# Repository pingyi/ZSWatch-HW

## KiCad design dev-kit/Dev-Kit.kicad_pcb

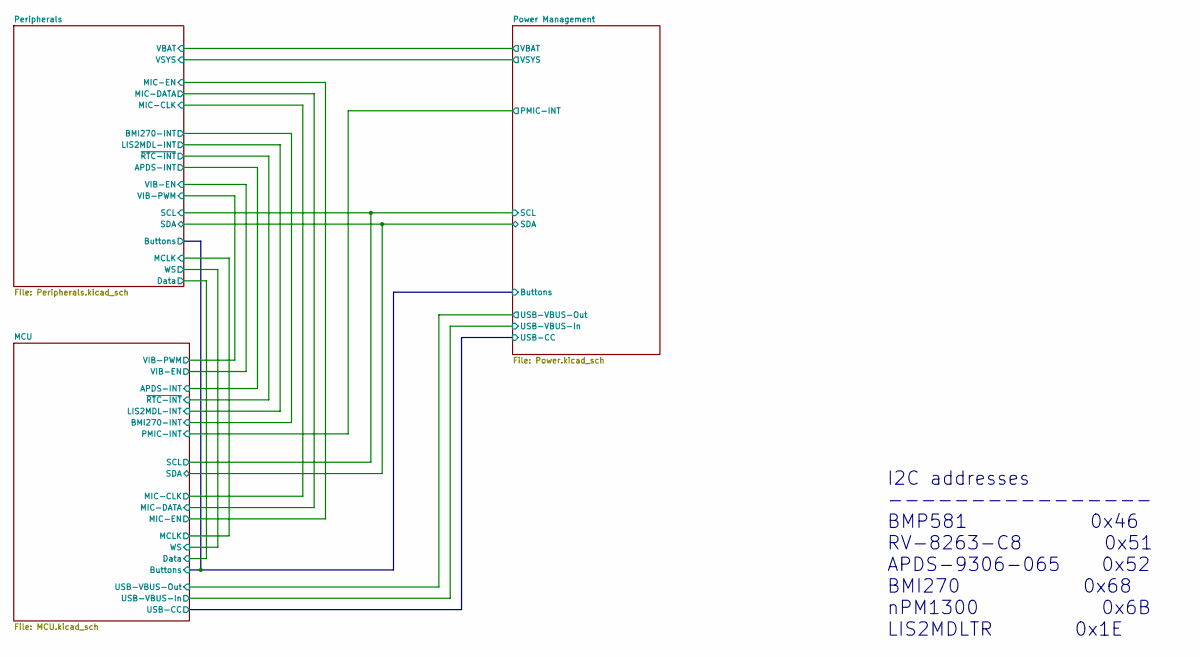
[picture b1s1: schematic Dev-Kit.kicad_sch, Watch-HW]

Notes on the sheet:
I2C addresses ---------------- BMP581 0x46 RV-8263-C8 0x51 APDS-9306-065 0x52 BMI270 0x68 nPM1300 0x6B LIS2MDLTR 0x1E

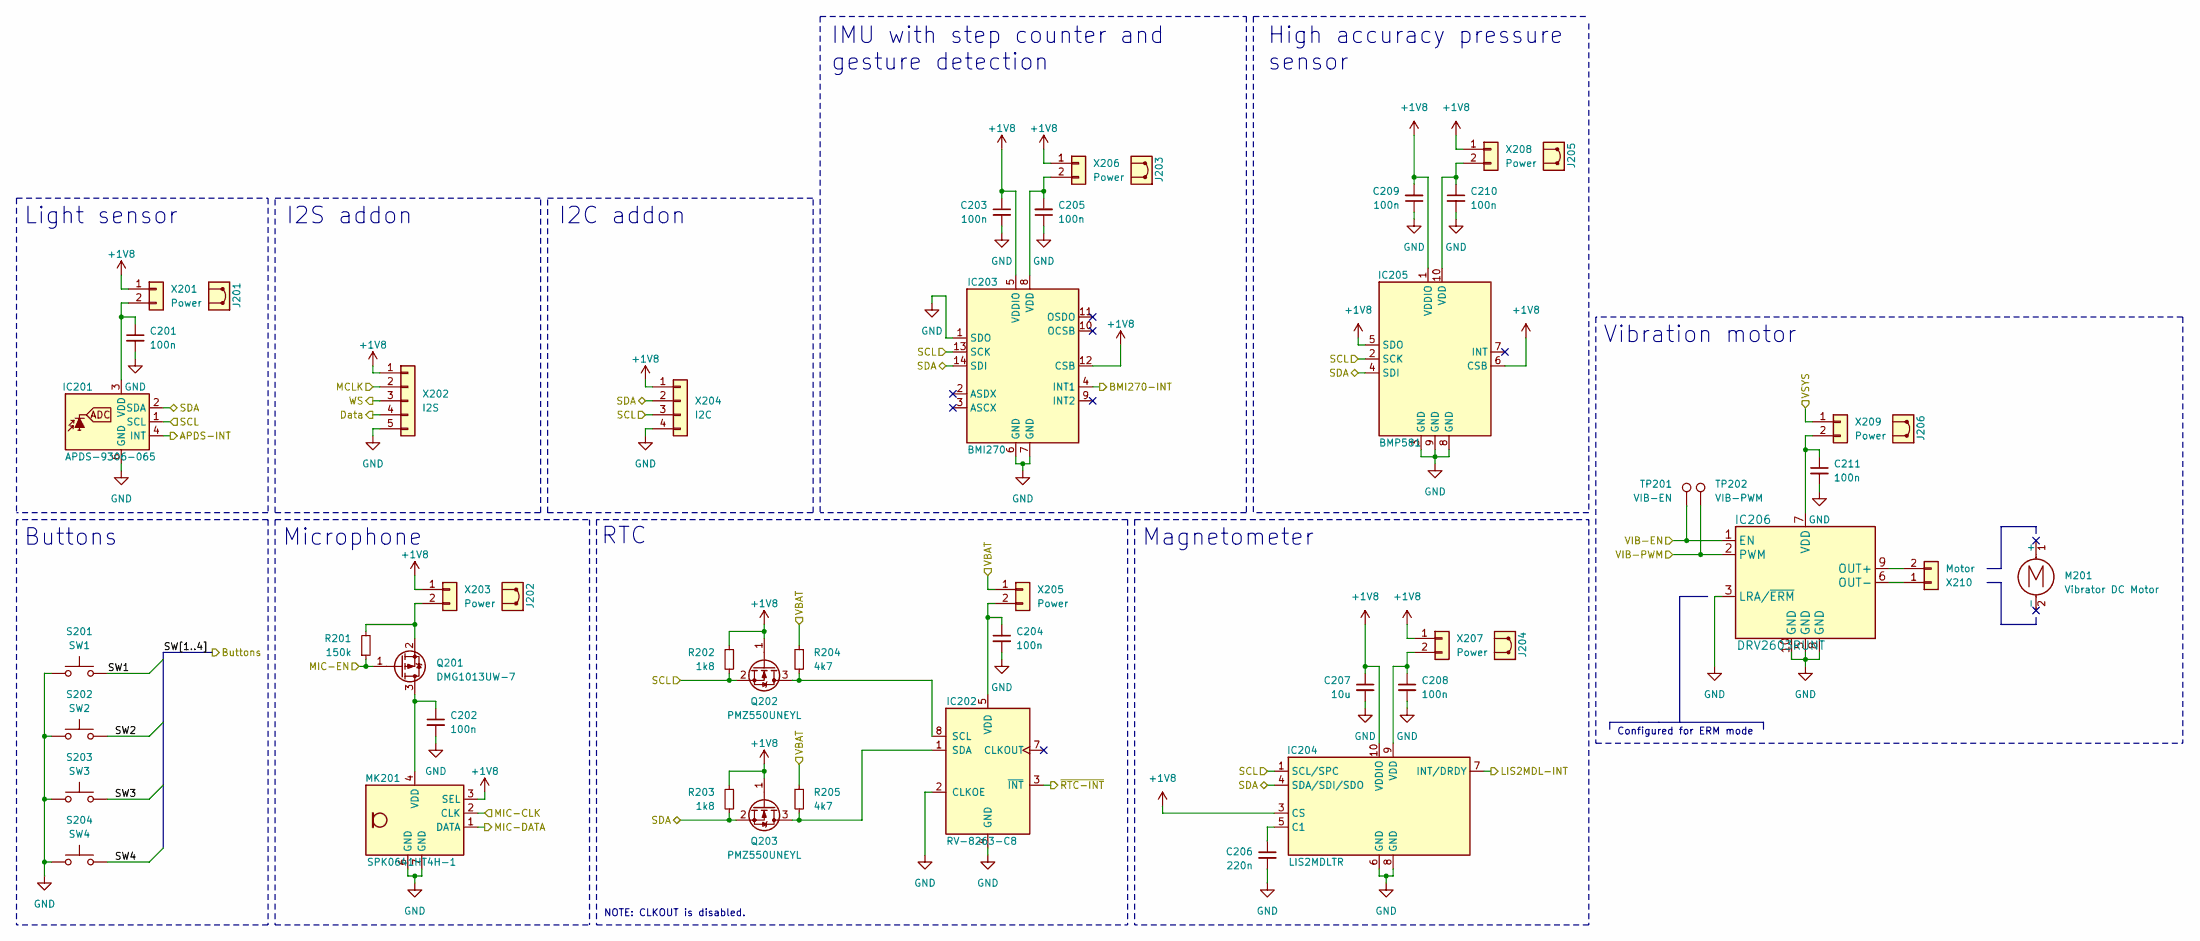
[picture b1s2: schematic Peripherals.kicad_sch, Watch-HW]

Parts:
C201, C202, C203, C204, C205, C208, C209, C210, C211: 100n; C_0402_1005Metric; mouser# 581-0402ZC104KAT4A
C206: 220n; C_0402_1005Metric; mouser# 581-04023C224KAT2A
C207: 10u; C_0402_1005Metric; mouser# 81-GRJ155R60J106ME11D
IC201: APDS-9306-065; Broadcom_DFN-6_2x2mm_P0.65mm; mouser# 630-APDS-9306-065
IC202: RV-8263-C8; mouser# 428-204291-MC01
IC203: BMI270; Bosch_LGA-14_3x2.5mm_P0.5mm_LayoutBorder3x4y; mouser# 262-BMI270
IC204: LIS2MDLTR; LGA-12_2x2mm_P0.5mm; mouser# 511-LIS2MDLTR
IC205: BMP581; Bosch_LGA-10_2x2mm_P0.5mm_ClockwisePinNumbering; mouser# 262-BMP581
IC206: DRV2603RUNT; WQFN-10_2x2mm_P0.5mm; mouser# 595-DRV2603RUNT
J201, J202, J203, J204, J205, J206: Jumper; mouser# 710-60900213421
M201: Vibrator DC Motor; digikey# 1670-VC1027B902F-ND
MK201: SPK0641HT4H-1; mouser# 721-SPK0641HT4H-1
Q201: DMG1013UW-7; SOT-323_SC-70; mouser# 621-DMG1013UW-7
Q202, Q203: PMZ550UNEYL; SOT-883; mouser# 771-PMZ550UNEYL
R201: 150k; R_0402_1005Metric; mouser# 603-RC0404FR-07150KL
R202, R203: 1k8; R_0402_1005Metric; mouser# 603-RC0402FR-074K7L
R204, R205: 4k7; R_0402_1005Metric; mouser# 603-RC0402FR-074K7L
S201: SW1; WS-TASV-6x6; mouser# 710-430182050816
S202: SW2; WS-TASV-6x6; mouser# 710-430182050816
S203: SW3; WS-TASV-6x6; mouser# 710-430182050816
S204: SW4; WS-TASV-6x6; mouser# 710-430182050816
TP201: VIB-EN; TestPoint_Pad_D1.0mm
TP202: VIB-PWM; TestPoint_Pad_D1.0mm
X201, X203, X205, X206, X207, X208, X209: Power; PinHeader_1x02_P2.54mm_Vertical_SMD_Pin1Left; mouser# 649-1012938090201BLF
X202: I2S; PinHeader_1x05_P2.54mm_Vertical_SMD_Pin1Left; mouser# 649-10129380-905002ALF
X204: I2C; PinHeader_1x04_P2.54mm_Vertical_SMD_Pin1Left; mouser# 649-10129380-904002ALF
X210: Motor; 78171-0002; mouser# 538-78171-0002

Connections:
+1V8: C203.1, C207.1, C209.2, IC203.5 (VDDIO), IC203.12 (CSB), IC204.3 (CS), IC204.10 (VDDIO), IC205.1 (VDDIO), IC205.5 (SDO), IC205.6 (CSB), MK201.3 (SEL), Q202.1 (G), Q203.1 (G), R202.1, R203.1, X201.1, X202.1, X203.1, X204.1, X206.1, X207.1, X208.1; also elsewhere on the board
/MCU/APDS-INT: IC201.4 (INT); also elsewhere on the board
/MCU/BMI270-INT: IC203.4 (INT1); also elsewhere on the board
/MCU/Data: X202.4; also elsewhere on the board
/MCU/LIS2MDL-INT: IC204.7 (INT/DRDY); also elsewhere on the board
/MCU/MCLK: X202.2; also elsewhere on the board
/MCU/MIC-CLK: MK201.2 (CLK); also elsewhere on the board
/MCU/MIC-DATA: MK201.1 (DATA); also elsewhere on the board
/MCU/MIC-EN: Q201.1 (G), R201.1; also elsewhere on the board
/MCU/SCL: IC201.1 (SCL), IC203.13 (SCK), IC204.1 (SCL/SPC), IC205.2 (SCK), Q202.2 (S), R202.2, X204.3; also elsewhere on the board
/MCU/SDA: IC201.2 (SDA), IC203.14 (SDI), IC204.4 (SDA/SDI/SDO), IC205.4 (SDI), Q203.2 (S), R203.2, X204.2; also elsewhere on the board
/MCU/SW1: S201.1; also elsewhere on the board
/MCU/SW2: S202.2; also elsewhere on the board
/MCU/SW3: S203.2; also elsewhere on the board
/MCU/SW4: S204.1; also elsewhere on the board
/MCU/VIB-EN: IC206.1 (EN), TP201.1; also elsewhere on the board
/MCU/VIB-PWM: IC206.2 (PWM), TP202.1; also elsewhere on the board
/MCU/WS: X202.3; also elsewhere on the board
/MCU/~RTC-INT: IC202.3 (~INT); also elsewhere on the board
/Peripherals/VBAT: R204.1, R205.1, X205.1; also elsewhere on the board
/Peripherals/VSYS: X209.1; also elsewhere on the board
GND: C201.2, C202.2, C203.2, C204.2, C205.1, C206.2, C207.2, C208.2, C209.1, C210.2, C211.2, IC201.6 (GND), IC202.2 (CLKOE), IC202.4 (GND), IC203.1 (SDO), IC203.6 (GND), IC203.7 (GND), IC204.6 (GND), IC204.8 (GND), IC205.3 (GND), IC205.8 (GND), IC205.9 (GND), IC206.3 (LRA/~ERM), IC206.5 (GND), IC206.8 (GND), IC206.10 (GND), MK201.5 (GND), MK201.6 (GND), MK201.7 (GND), MK201.8 (GND), S201.2, S202.1, S203.1, S204.2, X202.5, X204.4; also elsewhere on the board
unnamed: C201.1, IC201.3 (VDD), X201.2
unnamed: IC202.8 (SCL), Q202.3 (D), R204.2
unnamed: IC202.1 (SDA), Q203.3 (D), R205.2
unnamed: C204.1, IC202.5 (VDD), X205.2
unnamed: C205.2, IC203.8 (VDD), X206.2
unnamed: C206.1, IC204.5 (C1)
unnamed: C208.1, IC204.9 (VDD), X207.2
unnamed: C210.1, IC205.10 (VDD), X208.2
unnamed: IC206.9 (OUT+), X210.2
unnamed: IC206.6 (OUT-), X210.1
unnamed: C211.1, IC206.7 (VDD), X209.2
unnamed: C202.1, MK201.4 (VDD), Q201.3 (D)
unnamed: Q201.2 (S), R201.2, X203.2

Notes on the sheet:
Vibration motor
I2S addon
I2C addon
Magnetometer
Configured for ERM mode
High accuracy pressure sensor
Buttons
RTC
Microphone
Light sensor
IMU with step counter and gesture detection
NOTE: CLKOUT is disabled.

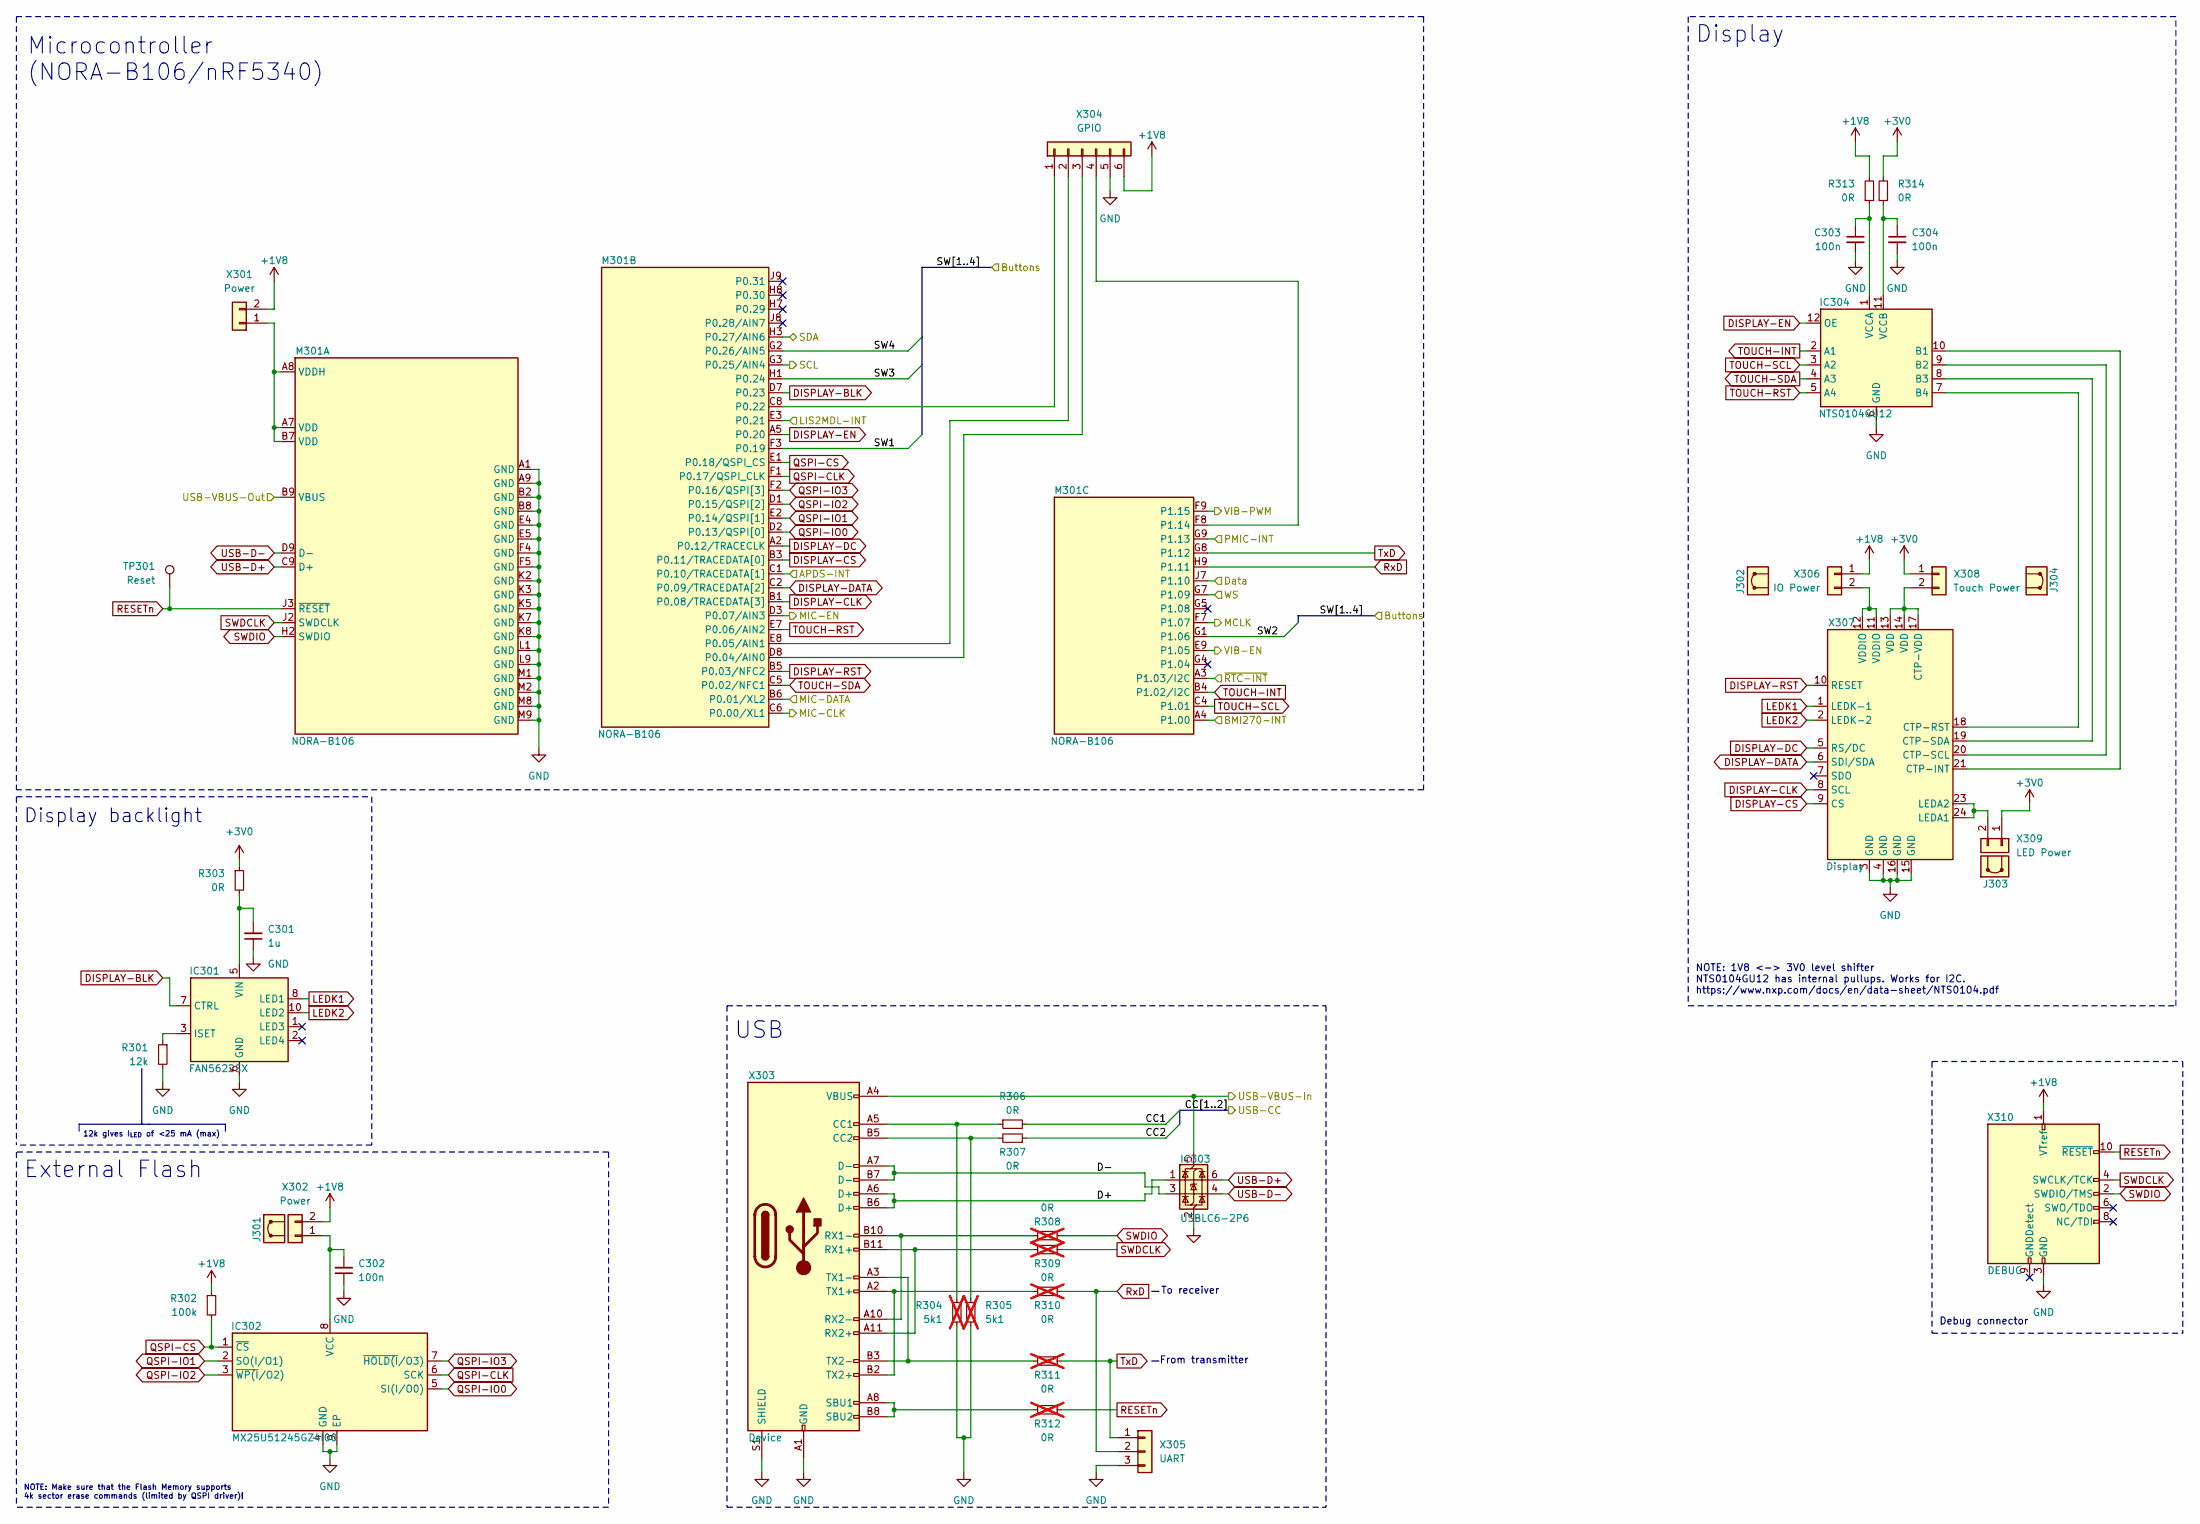
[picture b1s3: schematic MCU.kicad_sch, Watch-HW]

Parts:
C301: 1u; C_0402_1005Metric; mouser# 581-04023D105KAT2A
C302, C303, C304: 100n; C_0402_1005Metric; mouser# 581-0402ZC104KAT4A
IC301: FAN5622SX; UQFN-10_1.4x1.8mm_P0.4mm; mouser# 512-FAN5624UMPX
IC302: MX25U51245GZ4I00; WSON-8-1EP_8x6mm_P1.27mm_EP3.4x4.3mm; mouser# 95-25U51245GZ4I00T
IC303: USBLC6-2P6; SOT-666; mouser# 511-USBLC6-2P6
IC304: NTS0104GU12; XQFN-12-1.7x2mm_P0.4mm; mouser# 771-NTS0104GU12115
J301, J302, J303, J304: Jumper; mouser# 710-60900213421
M301: NORA-B106; mouser# 377-NORA-B106-00B
R301: 12k; R_0402_1005Metric; mouser# 603-RC0402FR-0712KL
R302: 100k; R_0402_1005Metric; mouser# 603-RC0404FR-07100KL
R303, R306, R307, R313, R314: 0R; R_0805_2012Metric; mouser# 652-CR0805-J/-000ELF
R304, R305: 5k1; R_0402_1005Metric; mouser# 652-CR0402-FX-5101GLF; not fitted
R308, R309, R310, R311, R312: 0R; R_0805_2012Metric; mouser# 652-CR0805-J/-000ELF; not fitted
TP301: Reset; TestPoint_Pad_D1.0mm
X301, X302: Power; PinHeader_1x02_P2.54mm_Vertical_SMD_Pin1Left; mouser# 649-1012938090201BLF
X303: Device; USB_C_Receptacle_Amphenol_12401610E4-2A; mouser# 523-12401610E4#2A
X304: GPIO; PinHeader_1x06_P2.54mm_Vertical_SMD_Pin1Left; mouser# 649-1012938090602ALF
X305: UART; PinHeader_1x03_P2.54mm_Vertical; mouser# 649-1012937893601BLF
X306: IO Power; PinHeader_1x02_P2.54mm_Vertical_SMD_Pin1Left; mouser# 649-1012938090201BLF
X307: Display; ER-CON0.4-24P
X308: Touch Power; PinHeader_1x02_P2.54mm_Vertical_SMD_Pin1Left; mouser# 649-1012938090201BLF
X309: LED Power; PinHeader_1x02_P2.54mm_Vertical_SMD_Pin1Left; mouser# 649-1012938090201BLF
X310: DEBUG; PinHeader_2x05_P1.27mm_Vertical; mouser# 200-SHF-105-01-L-D-TH-TR

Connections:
+1V8: R302.1, R313.2, X301.2, X302.2, X304.6, X306.1, X310.1 (VTref); also elsewhere on the board
+3V0: R303.1, R314.2, X308.1, X309.1; also elsewhere on the board
/MCU/APDS-INT: M301.C1 (P0.10/TRACEDATA[1]); also elsewhere on the board
/MCU/BMI270-INT: M301.A4 (P1.00); also elsewhere on the board
/MCU/CC1: R306.2; also elsewhere on the board
/MCU/CC2: R307.1; also elsewhere on the board
/MCU/D+: IC303.1 (I/O1), X303.A6 (D+), X303.B6 (D+)
/MCU/D-: IC303.3 (I/O2), X303.A7 (D-), X303.B7 (D-)
/MCU/Data: M301.J7 (P1.10); also elsewhere on the board
/MCU/LIS2MDL-INT: M301.E3 (P0.21); also elsewhere on the board
/MCU/MCLK: M301.F7 (P1.07); also elsewhere on the board
/MCU/MIC-CLK: M301.C6 (P0.00/XL1); also elsewhere on the board
/MCU/MIC-DATA: M301.B6 (P0.01/XL2); also elsewhere on the board
/MCU/MIC-EN: M301.D3 (P0.07/AIN3); also elsewhere on the board
/MCU/PMIC-INT: M301.G9 (P1.13); also elsewhere on the board
/MCU/SCL: M301.G3 (P0.25/AIN4); also elsewhere on the board
/MCU/SDA: M301.H3 (P0.27/AIN6); also elsewhere on the board
/MCU/SW1: M301.F3 (P0.19); also elsewhere on the board
/MCU/SW2: M301.G1 (P1.06); also elsewhere on the board
/MCU/SW3: M301.H1 (P0.24); also elsewhere on the board
/MCU/SW4: M301.G2 (P0.26/AIN5); also elsewhere on the board
/MCU/USB-VBUS-In: IC303.5 (VBUS), X303.A4 (VBUS), X303.A9 (VBUS), X303.B4 (VBUS), X303.B9 (VBUS); also elsewhere on the board
/MCU/USB-VBUS-Out: M301.B9 (VBUS); also elsewhere on the board
/MCU/VIB-EN: M301.E9 (P1.05); also elsewhere on the board
/MCU/VIB-PWM: M301.F9 (P1.15); also elsewhere on the board
/MCU/WS: M301.G7 (P1.09); also elsewhere on the board
/MCU/~RTC-INT: M301.A3 (P1.03/I2C); also elsewhere on the board
DISPLAY-BLK: IC301.7 (CTRL), M301.D7 (P0.23)
DISPLAY-CLK: M301.B1 (P0.08/TRACEDATA[3]), X307.8 (SCL)
DISPLAY-CS: M301.B3 (P0.11/TRACEDATA[0]), X307.9 (CS)
DISPLAY-DATA: M301.C2 (P0.09/TRACEDATA[2]), X307.6 (SDI/SDA)
DISPLAY-DC: M301.A2 (P0.12/TRACECLK), X307.5 (RS/DC)
DISPLAY-EN: IC304.12 (OE), M301.A5 (P0.20)
DISPLAY-RST: M301.B5 (P0.03/NFC2), X307.10 (RESET)
GND: C301.1, C302.1, C303.2, C304.2, IC301.6 (GND), IC302.4 (GND), IC302.9 (EP), IC303.2 (GND), IC304.6 (GND), M301.A1 (GND), M301.A9 (GND), M301.B2 (GND), M301.B8 (GND), M301.E4 (GND), M301.E5 (GND), M301.F4 (GND), M301.F5 (GND), M301.K2 (GND), M301.K3 (GND), M301.K5 (GND), M301.K7 (GND), M301.K8 (GND), M301.L1 (GND), M301.L9 (GND), M301.M1 (GND), M301.M2 (GND), M301.M8 (GND), M301.M9 (GND), R301.2, R304.2, R305.1, X303.A1 (GND), X303.A12 (GND), X303.B1 (GND), X303.B12 (GND), X303.S1 (SHIELD), X304.5, X305.3, X307.3 (GND), X307.4 (GND), X307.15 (GND), X307.16 (GND), X310.3 (GND), X310.5 (GND); also elsewhere on the board
LEDK1: IC301.8 (LED1), X307.1 (LEDK-1)
LEDK2: IC301.10 (LED2), X307.2 (LEDK-2)
unnamed: IC301.3 (ISET), R301.1
unnamed: C301.2, IC301.5 (VIN), R303.2
unnamed: C302.2, IC302.8 (VCC), X302.1
unnamed: IC304.10 (B1), X307.21 (CTP-INT)
unnamed: IC304.9 (B2), X307.20 (CTP-SCL)
unnamed: IC304.8 (B3), X307.19 (CTP-SDA)
unnamed: IC304.7 (B4), X307.18 (CTP-RST)
unnamed: C303.1, IC304.1 (VCCA), R313.1
unnamed: C304.1, IC304.11 (VCCB), R314.1
unnamed: M301.A7 (VDD), M301.A8 (VDDH), M301.B7 (VDD), X301.1
unnamed: M301.D8 (P0.04/AIN0), X304.3
unnamed: M301.E8 (P0.05/AIN1), X304.2
unnamed: M301.C8 (P0.22), X304.1
unnamed: M301.F8 (P1.14), X304.4
unnamed: R304.1, R306.1, X303.A5 (CC1)
unnamed: R305.2, R307.2, X303.B5 (CC2)
unnamed: R309.2, X303.A11 (RX2+), X303.B11 (RX1+)
unnamed: R308.2, X303.A10 (RX2-), X303.B10 (RX1-)
unnamed: R312.2, X303.A8 (SBU1), X303.B8 (SBU2)
unnamed: R310.2, X303.A2 (TX1+), X303.B2 (TX2+)
unnamed: R311.2, X303.A3 (TX1-), X303.B3 (TX2-)
unnamed: X306.2, X307.11 (VDDIO), X307.12 (VDDIO)
unnamed: X307.13 (VDD), X307.14 (VDD), X307.17 (CTP-VDD), X308.2
unnamed: X307.23 (LEDA2), X307.24 (LEDA1), X309.2
QSPI-CLK: IC302.6 (SCK), M301.F1 (P0.17/QSPI_CLK)
QSPI-CS: IC302.1 (~CS), M301.E1 (P0.18/QSPI_CS), R302.2
QSPI-IO0: IC302.5 (SI(I/O0)), M301.D2 (P0.13/QSPI[0])
QSPI-IO1: IC302.2 (SO(I/O1)), M301.E2 (P0.14/QSPI[1])
QSPI-IO2: IC302.3 (~WP(I/O2)), M301.D1 (P0.15/QSPI[2])
QSPI-IO3: IC302.7 (~HOLD(I/O3)), M301.F2 (P0.16/QSPI[3])
RESETn: M301.J3 (~RESET), R312.1, TP301.1, X310.10 (~RESET)
RxD: M301.H9 (P1.11), R310.1, X305.2
SWDCLK: M301.J2 (SWDCLK), R309.1, X310.4 (SWCLK/TCK)
SWDIO: M301.H2 (SWDIO), R308.1, X310.2 (SWDIO/TMS)
TOUCH-INT: IC304.2 (A1), M301.B4 (P1.02/I2C)
TOUCH-RST: IC304.5 (A4), M301.E7 (P0.06/AIN2)
TOUCH-SCL: IC304.3 (A2), M301.C4 (P1.01)
TOUCH-SDA: IC304.4 (A3), M301.C5 (P0.02/NFC1)
TxD: M301.G8 (P1.12), R311.1, X305.1
USB-D+: IC303.6 (I/O1), M301.C9 (D+)
USB-D-: IC303.4 (I/O2), M301.D9 (D-)

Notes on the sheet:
From transmitter
To receiver
12k gives I_{LED} of <25 mA (max)
NOTE: Make sure that the Flash Memory supports 4k sector erase commands (limited by QSPI driver)!
Display
Debug connector
USB
NOTE: 1V8 <-> 3V0 level shifter NTS0104GU12 has internal pullups. Works for I2C. https://www.nxp.com/docs/en/data-sheet/NTS0104.pdf
Microcontroller (NORA-B106/nRF5340)
Display backlight
External Flash

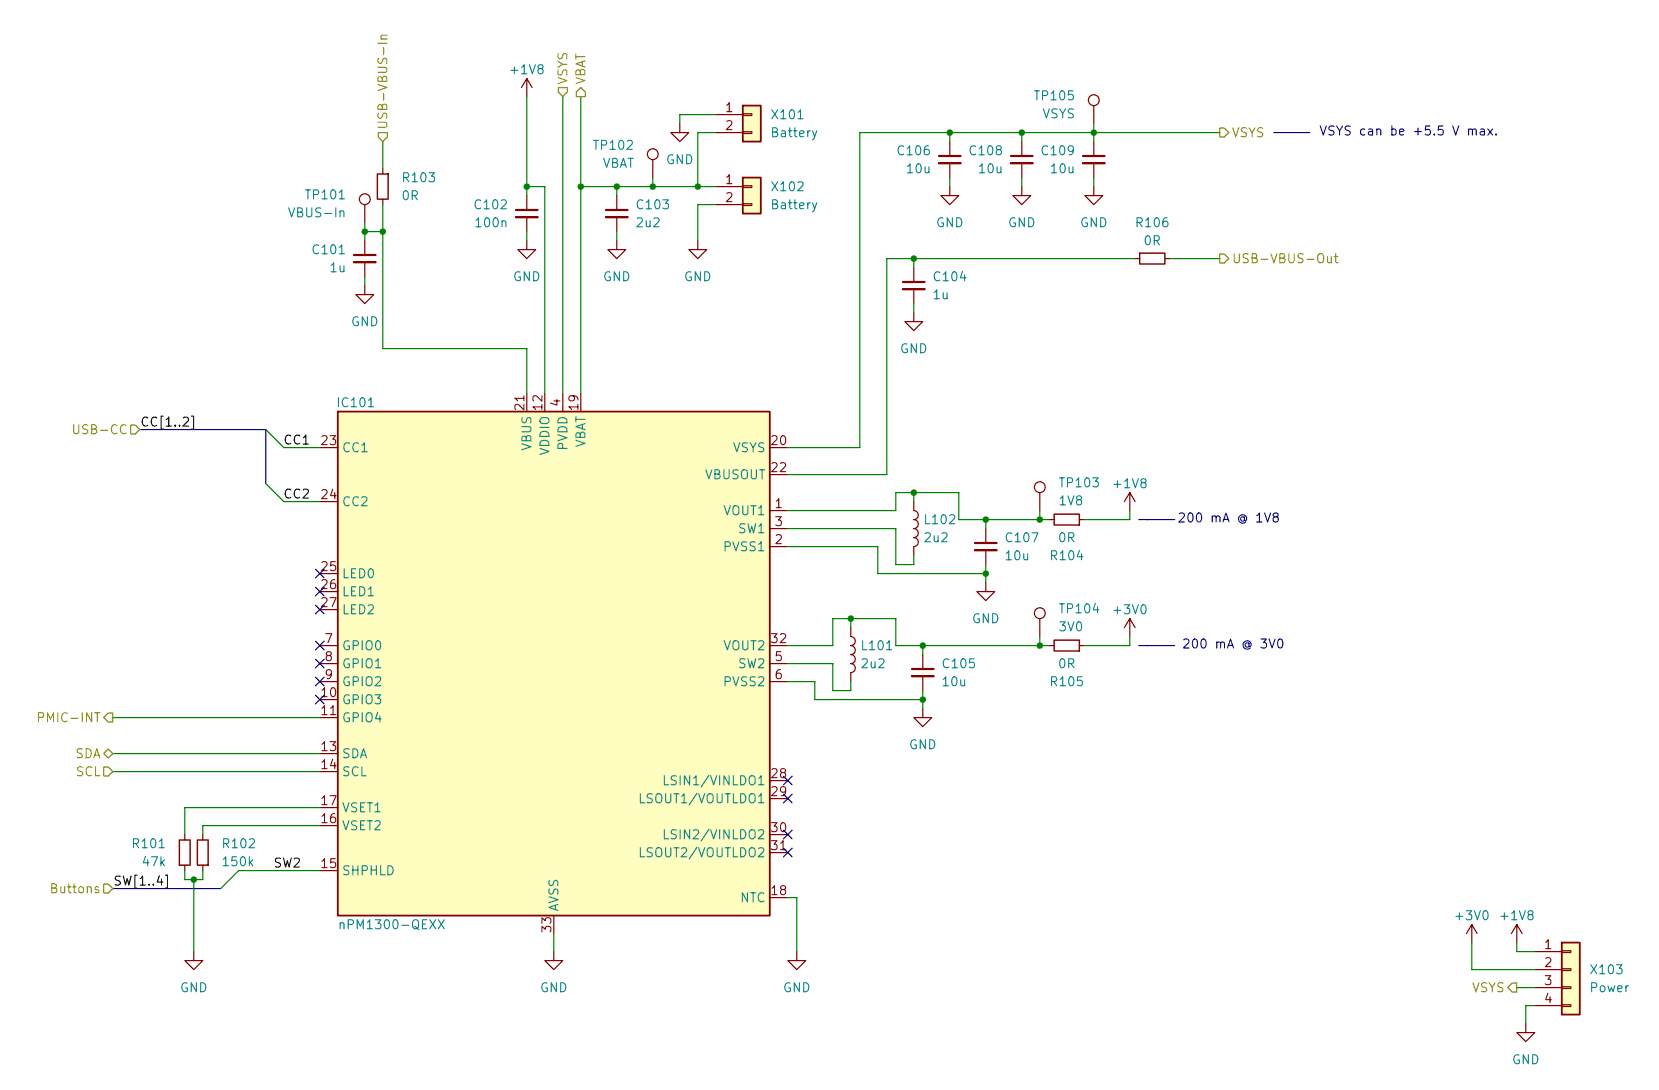
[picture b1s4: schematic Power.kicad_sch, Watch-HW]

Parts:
C101, C104: 1u; C_0402_1005Metric; mouser# 581-04023D105KAT2A
C102: 100n; C_0402_1005Metric; mouser# 581-0402ZC104KAT4A
C103: 2u2; C_0402_1005Metric; mouser# 581-04026D105MAT4A
C105, C107: 10u; C_0402_1005Metric; mouser# 81-GRJ155R60J106ME11D
C106, C108, C109: 10u; C_0603_1608Metric; mouser# 581-KGM15CR50J106MT
IC101: nPM1300-QEXX; QFN-32-1EP_5x5mm_P0.5mm_EP3.6x3.6mm_ThermalVias; mouser# 949-NPM1300-QEAA-R7
L101, L102: 2u2; L_0806_2016; mouser# 815-ASMPH-0806-2R2M-T
R101: 47k; R_0402_1005Metric; mouser# 603-RC0402FR-0747KL
R102: 150k; R_0402_1005Metric; mouser# 603-RC0402FR-07150KL
R103, R104, R105, R106: 0R; R_0805_2012Metric; mouser# 652-CR0805-J/-000ELF
TP101: VBUS-In; TestPoint_Pad_D1.0mm
TP102: VBAT; TestPoint_Pad_D1.0mm
TP103: 1V8; TestPoint_Pad_D1.0mm
TP104: 3V0; TestPoint_Pad_D1.0mm
TP105: VSYS; TestPoint_Pad_D1.0mm
X101: Battery; PinHeader_1x02_P2.54mm_Vertical; mouser# 649-1012938090201BLF
X102: Battery; 78171-0002; mouser# 538-78171-0002
X103: Power; PinHeader_1x04_P2.54mm_Vertical; mouser# 649-10129380-904002ALF

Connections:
+1V8: C102.1, IC101.12 (VDDIO), R104.1, X103.1; also elsewhere on the board
+3V0: R105.1, X103.2; also elsewhere on the board
/MCU/CC1: IC101.23 (CC1); also elsewhere on the board
/MCU/CC2: IC101.24 (CC2); also elsewhere on the board
/MCU/PMIC-INT: IC101.11 (GPIO4); also elsewhere on the board
/MCU/SCL: IC101.14 (SCL); also elsewhere on the board
/MCU/SDA: IC101.13 (SDA); also elsewhere on the board
/MCU/SW2: IC101.15 (SHPHLD); also elsewhere on the board
/MCU/USB-VBUS-In: R103.1; also elsewhere on the board
/MCU/USB-VBUS-Out: R106.2; also elsewhere on the board
/Peripherals/VBAT: C103.1, IC101.19 (VBAT), TP102.1, X101.2, X102.1; also elsewhere on the board
/Peripherals/VSYS: C106.1, C108.1, C109.1, IC101.4 (PVDD), IC101.20 (VSYS), TP105.1, X103.3; also elsewhere on the board
GND: C101.2, C102.2, C103.2, C104.2, C105.2, C106.2, C107.2, C108.2, C109.2, IC101.2 (PVSS1), IC101.6 (PVSS2), IC101.18 (NTC), IC101.33 (AVSS), R101.1, R102.1, X101.1, X102.2, X103.4; also elsewhere on the board
unnamed: IC101.3 (SW1), L102.2
unnamed: IC101.5 (SW2), L101.2
unnamed: C101.1, IC101.21 (VBUS), R103.2, TP101.1
unnamed: C104.1, IC101.22 (VBUSOUT), R106.1
unnamed: C107.1, IC101.1 (VOUT1), L102.1, R104.2, TP103.1
unnamed: C105.1, IC101.32 (VOUT2), L101.1, R105.2, TP104.1
unnamed: IC101.17 (VSET1), R101.2
unnamed: IC101.16 (VSET2), R102.2

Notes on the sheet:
200 mA @ 1V8
VSYS can be +5.5 V max.
200 mA @ 3V0

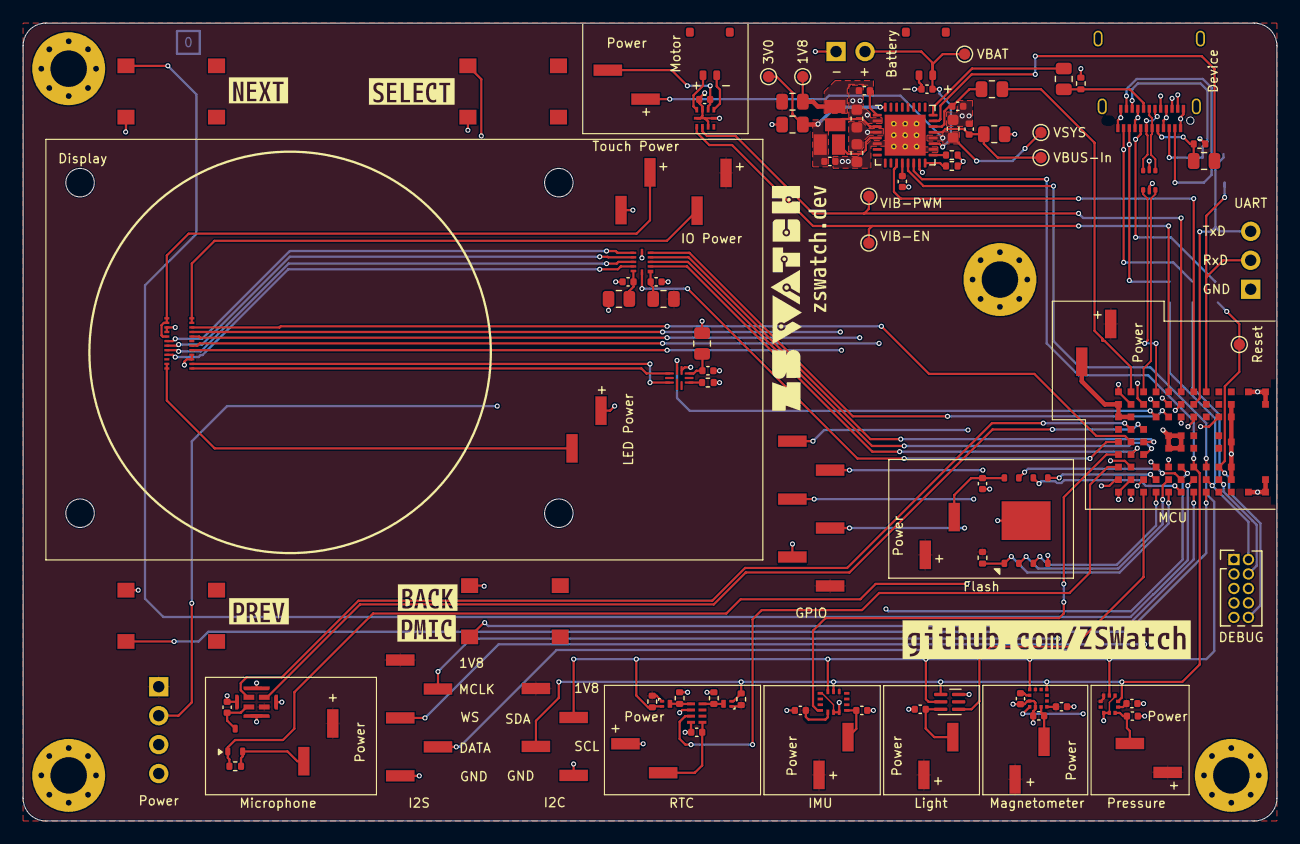
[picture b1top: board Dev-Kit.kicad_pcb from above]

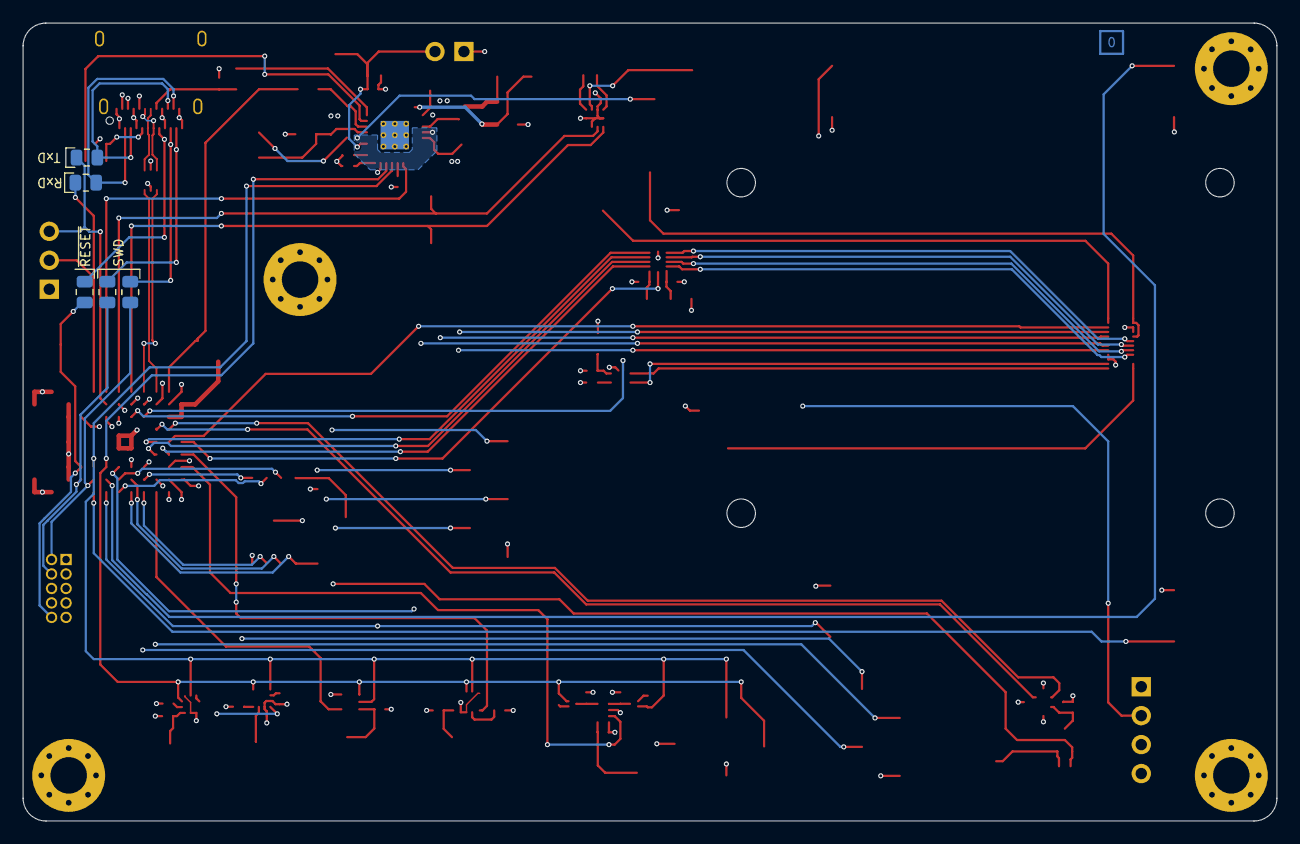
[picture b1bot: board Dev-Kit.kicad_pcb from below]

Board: 4 copper layers, 110.0 x 70.0 mm, 109 parts (5 on the bottom side), 101 nets.

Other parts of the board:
kibuzzard-683075F5: G***; kibuzzard-683075F5
kibuzzard-6830428E: G***; kibuzzard-6830428E
kibuzzard-68303879: G***; kibuzzard-68303879
kibuzzard-68304278: G***; kibuzzard-68304278
kibuzzard-68304289: G***; kibuzzard-68304289
kibuzzard-68304292: G***; kibuzzard-68304292
kibuzzard-68304463: G***; kibuzzard-68304463

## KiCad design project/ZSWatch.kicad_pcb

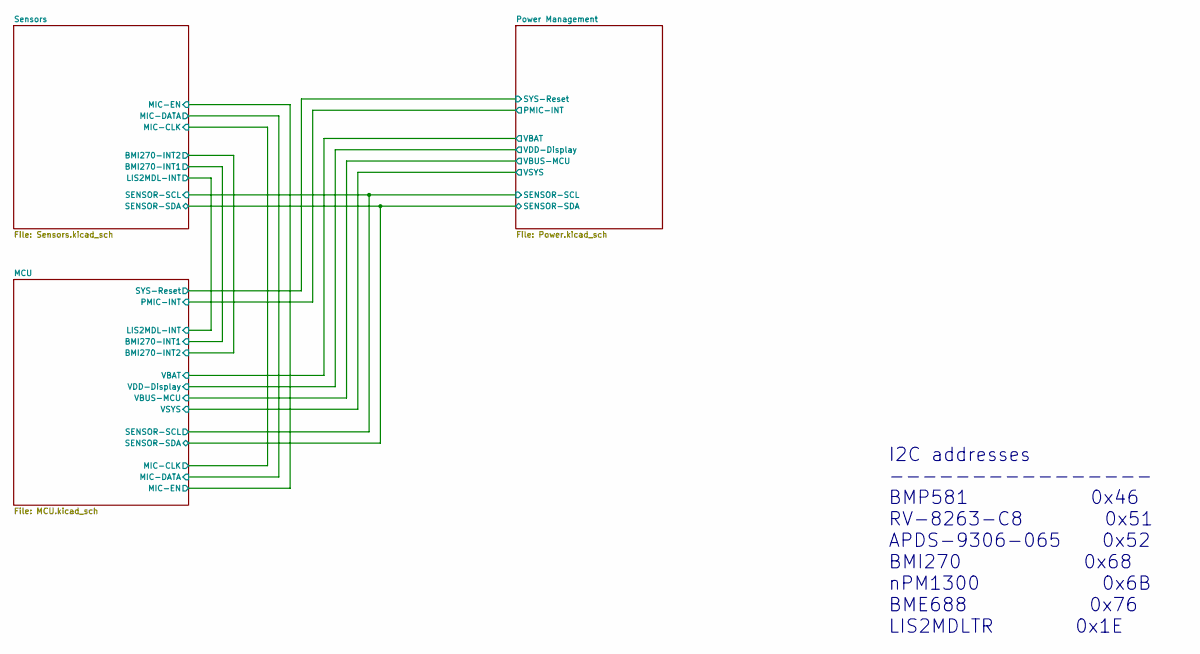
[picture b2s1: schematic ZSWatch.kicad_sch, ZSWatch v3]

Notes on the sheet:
I2C addresses ---------------- BMP581 0x46 RV-8263-C8 0x51 APDS-9306-065 0x52 BMI270 0x68 nPM1300 0x6B BME688 0x76 LIS2MDLTR 0x1E
